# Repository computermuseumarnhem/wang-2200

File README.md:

# Wang 2200

I'd like to get this thing working again.

Therefore:

## Extension cards

I've created extension cards to be able to raise the the processor and interface cards out of the card cage. The boards are 8" (203.20 mm) long 
and 2.50" (63.5 mm) wide. In total three extension cards are needed for a full processor board, and two for an interface card, or the power regulator
card.

Features are:

- The card is raised outside the card cage and rotated 90 degrees (component side up). That makes it easy to probe signals with a multimeter or oscilloscope.
- A standard 2x15 0.1" header is provided that connects to all connection points on the card edge, for easy attachment of logic analyzer probes

## Power supply

The power supply consists of three parts

1. The transformer, the bulk filter capacitors, and a few resistors and diodes on the main board
2. The regulator board with the low power parts of the (linear) regulators (board L567)
3. The heat sink with the high power parts of the regulators (transistors and rectifiers)

The transformer and bulk filter capacitors are either soldered or screwed to the main board. The resistors and diodes are also soldered on the mainboard.

The regulator board is using the regular card edges (two 2 &times; 15 pads), also used on the other boards. These card edges mate with EDAC 307-030-520-201 card edge connectors.

The heat sink uses two TE Commercial MATE-N-LOK connectors, one 12 position (1-480287-0) and one 16 position (1-480438-0). The regulator board connects to the heat sink via the main board.

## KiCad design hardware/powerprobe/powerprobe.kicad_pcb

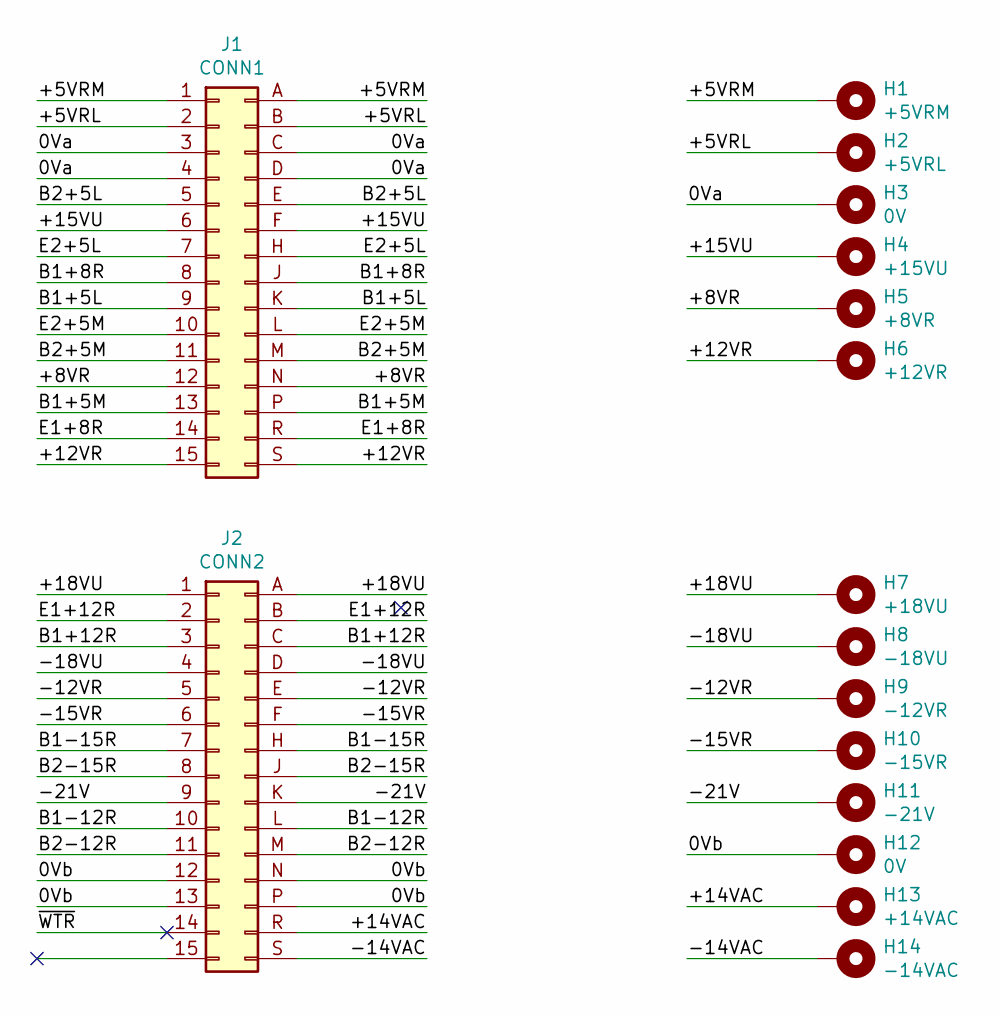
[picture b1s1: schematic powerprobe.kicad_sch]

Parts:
H1: +5VRM; MountingHole_4mm_Pad
H2: +5VRL; MountingHole_4mm_Pad
H3, H12: 0V; MountingHole_4mm_Pad
H4: +15VU; MountingHole_4mm_Pad
H5: +8VR; MountingHole_4mm_Pad
H6: +12VR; MountingHole_4mm_Pad
H7: +18VU; MountingHole_4mm_Pad
H8: -18VU; MountingHole_4mm_Pad
H9: -12VR; MountingHole_4mm_Pad
H10: -15VR; MountingHole_4mm_Pad
H11: -21V; MountingHole_4mm_Pad
H13: +14VAC; MountingHole_4mm_Pad
H14: -14VAC; MountingHole_4mm_Pad
J1: CONN1; PinSocket_2x15_P2.54mm_Horizontal
J2: CONN2; PinSocket_2x15_P2.54mm_Horizontal

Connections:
/0Va: H3.1, J1.3, J1.4, J1.C, J1.D
/0Vb: H12.1, J2.12, J2.13, J2.N, J2.P
/+5VRL: H2.1, J1.2, J1.B
/+5VRM: H1.1, J1.1, J1.A
/+8VR: H5.1, J1.12, J1.N
/+12VR: H6.1, J1.15, J1.S
/+14VAC: H13.1, J2.R
/+15VU: H4.1, J1.6, J1.F (G)
/+18VU: H7.1, J2.1, J2.A
/-12VR: H9.1, J2.5, J2.E
/-14VAC: H14.1, J2.S
/-15VR: H10.1, J2.6, J2.F (G)
/-18VU: H8.1, J2.4, J2.D
/-21V: H11.1, J2.9, J2.K
/B1+5L: J1.9, J1.K
/B1+5M: J1.13, J1.P
/B1+8R: J1.8, J1.J
/B1+12R: J2.3, J2.C
/B1-12R: J2.10, J2.L
/B1-15R: J2.7, J2.H
/B2+5L: J1.5, J1.E
/B2+5M: J1.11, J1.M
/B2-12R: J2.11, J2.M
/B2-15R: J2.8, J2.J
/E1+8R: J1.14, J1.R
/E1+12R: J2.2, J2.B
/E2+5L: J1.7, J1.H
/E2+5M: J1.10, J1.L

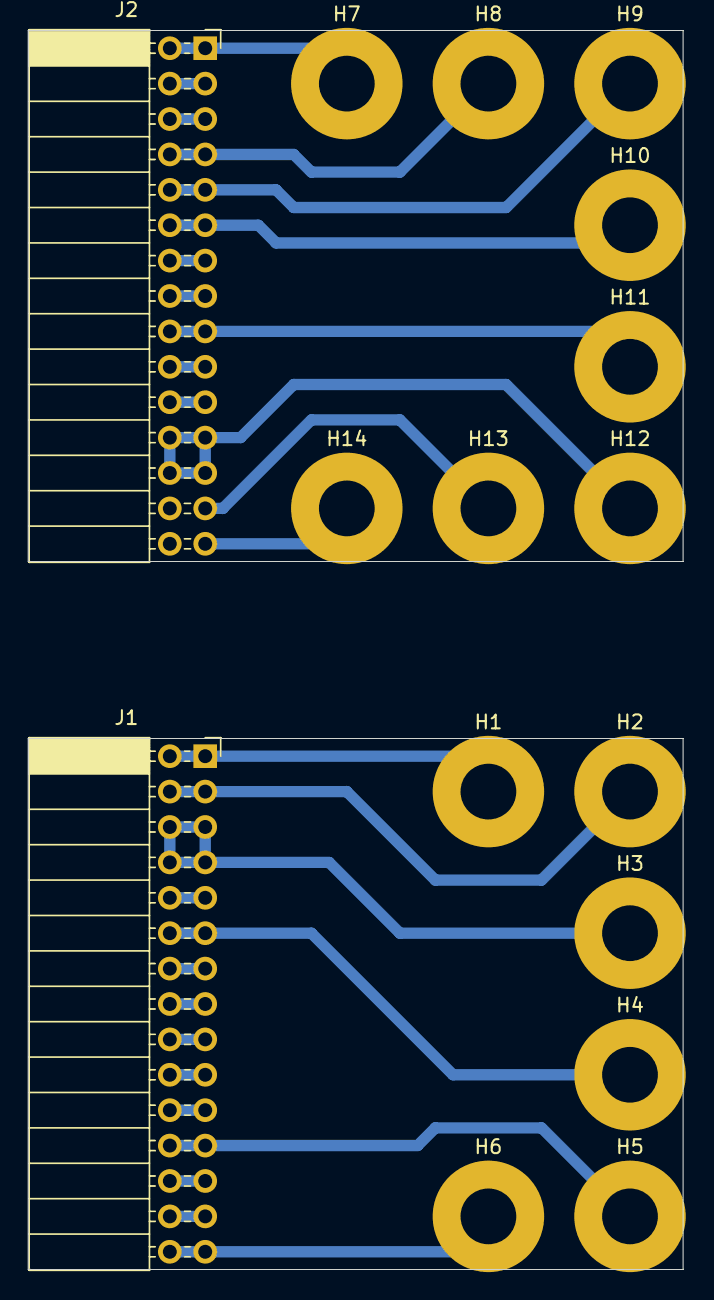
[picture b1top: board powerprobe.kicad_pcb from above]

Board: 2 copper layers, 47.0 x 88.9 mm, 16 parts (0 on the bottom side), 28 nets.

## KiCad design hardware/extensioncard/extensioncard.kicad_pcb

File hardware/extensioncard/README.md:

# Extension card

I've created an extension card to be able to raise the the processor and interface cards out of the card cage. The boards are 8" (203.20 mm) long and 2.50" (63.5 mm) wide. In total three extension cards are needed for a full processor board, and two for an interface card, or the power regulator card.

## Features

- The card is raised outside the card cage and rotated 90 degrees (component side up). That makes it easy to probe signals with a multimeter or oscilloscope.
- A standard 2x15 0.1" header is provided that connects to all connection points on the card edge, for easy attachment of logic analyzer probes

## Design

The PCB is designed in [KiCad], and the gerbers were sent to [JLCPCB] for manufacturing. The boards came back nice and have been used to check the power supply.

## Parts

- J1: Male card edge (not really a physical part)
- J2: Female card edge connector EDAC 307-030-520-201 [Datasheet] [Mouser]
- J3: Male pin header (2x15)

----
 \
Alex van Denzel denz@hack42.nl

[KiCad]: https://www.kicad.org/
[JLCPCB]: https://jlcpcb.com/
[Datasheet]: ../../documentation/307-030-520-201%20-%20EDAC%20Card%20Edge%20Connector.pdf
[Mouser]: https://nl.mouser.com/ProductDetail/EDAC/307-030-520-201?qs=aCtAaaGuzsYJID3KFF7AAw%3D%3D

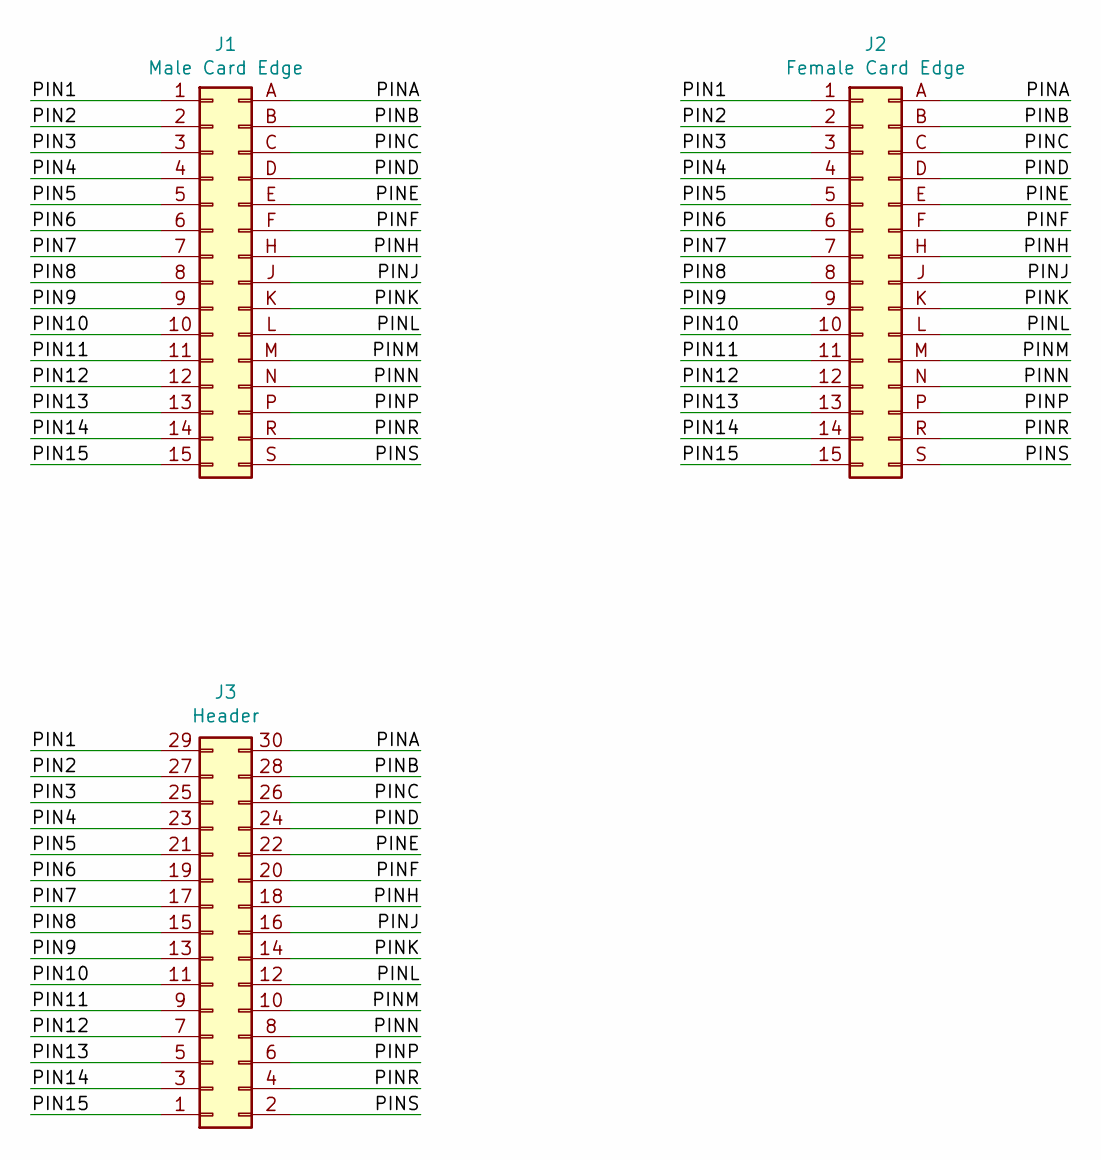
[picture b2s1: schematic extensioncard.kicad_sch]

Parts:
J1: Male Card Edge; Wang2200_02x15_CardEdge
J2: Female Card Edge; Wang2200_02x15_Connector
J3: Header; PinHeader_2x15_P2.54mm_Vertical

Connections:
/PIN1: J1.1, J2.1, J3.29
/PIN2: J1.2, J2.2, J3.27
/PIN3: J1.3, J2.3, J3.25
/PIN4: J1.4, J2.4, J3.23
/PIN5: J1.5, J2.5, J3.21
/PIN6: J1.6, J2.6, J3.19
/PIN7: J1.7, J2.7, J3.17
/PIN8: J1.8, J2.8, J3.15
/PIN9: J1.9, J2.9, J3.13
/PIN10: J1.10, J2.10, J3.11
/PIN11: J1.11, J2.11, J3.9
/PIN12: J1.12, J2.12, J3.7
/PIN13: J1.13, J2.13, J3.5
/PIN14: J1.14, J2.14, J3.3
/PIN15: J1.15, J2.15, J3.1
/PINA: J1.A, J2.A, J3.30
/PINB: J1.B, J2.B, J3.28
/PINC: J1.C, J2.C, J3.26
/PIND: J1.D, J2.D, J3.24
/PINE: J1.E, J2.E, J3.22
/PINF: J1.F (G), J2.F (G), J3.20
/PINH: J1.H, J2.H, J3.18
/PINJ: J1.J, J2.J, J3.16
/PINK: J1.K, J2.K, J3.14
/PINL: J1.L, J2.L, J3.12
/PINM: J1.M, J2.M, J3.10
/PINN: J1.N, J2.N, J3.8
/PINP: J1.P, J2.P, J3.6
/PINR: J1.R, J2.R, J3.4
/PINS: J1.S, J2.S, J3.2

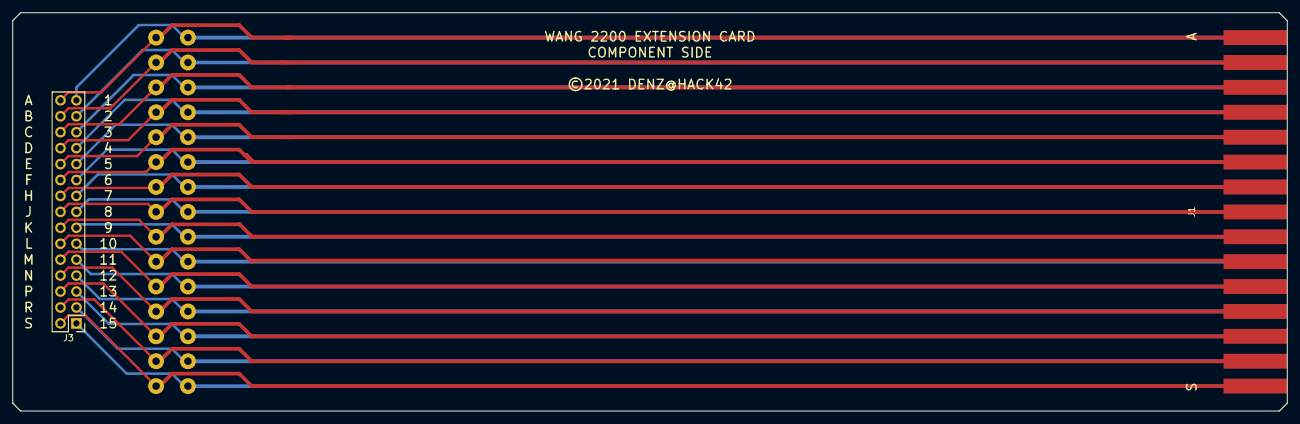
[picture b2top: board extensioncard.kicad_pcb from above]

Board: 2 copper layers, 203.2 x 63.5 mm, 3 parts (1 on the bottom side), 30 nets.

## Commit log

2021-03-18 initial
2021-03-19 extensioncard hopefully done
2021-06-13 some power supply updates
2024-01-12 documented extensioncard
2024-01-12 upcycled to newer version KiCad
2024-10-08 resized some pages in pdf
2024-10-08 small update in schematic
2025-09-13 moved extensioncard away

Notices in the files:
hardware/extensioncard/README.md:
CC BY-SA 4.0
hardware/extensioncard/extensioncard.kicad_pcb:
©2021 DENZ@HACK42
